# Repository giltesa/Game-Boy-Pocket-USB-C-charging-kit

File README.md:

# Game Boy Pocket USB-C Charging Kit

( This project is a fork from my  )

The **Game Boy Pocket USB-C Charging Kit** is a circuit that allows you to charge a **Nintendo Game Boy Pocket** by **USB-C** and use a **Li-ion** battery instead of AA batteries.

This circuit includes the famous **TP4056** and **DW01A**. The first one is the device in charge of charging the battery, and the second one is protecting the lifetime of the battery of the over-discharge.

This kit includes two boards. If you want to install it easy, it's enough with the main board which doesn't need any cable for working. However, if you want to have the status LEDs in the same place as the original status LED, then you will need to solder the second board and joint both with 3 cables. You can choose the best option for you.

This kit contains 3 boards:

- USB-C board
- Main board
- LEDs board

## Youtube:

Game Boy Pocket USB-C Charging Kit (Installation)

## Would you like it?

https://shop.giltesa.com/product/game-boy-pocket-usb-c-charging-kit/

## More

- [giltesa.com](https://giltesa.com "giltesa.com")
- [twitter.com](https://twitter.com/giltesa "twitter.com")

## License

This project is licensed under a **Creative Commons** license:
**[Attribution-NonCommercial-ShareAlike 4.0 International (CC BY-NC-SA 4.0) ](https://creativecommons.org/licenses/by-nc-sa/4.0/)**

Check the [LICENSE.md](LICENSE.md) for more information.

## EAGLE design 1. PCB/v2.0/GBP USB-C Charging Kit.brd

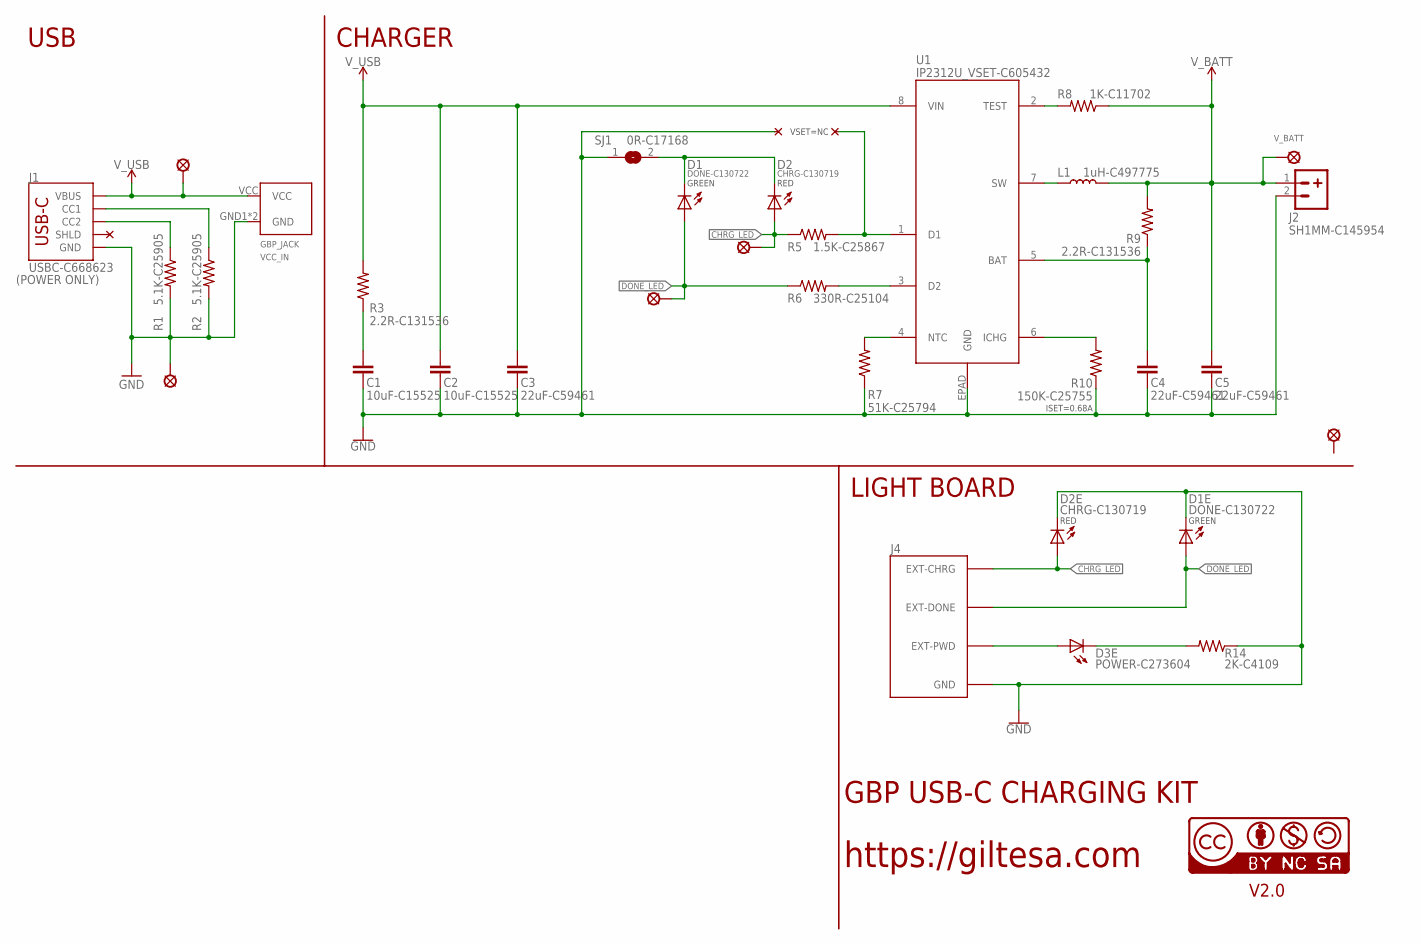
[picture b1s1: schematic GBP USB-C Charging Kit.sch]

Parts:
C1, C2: 10uF-C15525; C0402_S
C3, C4, C5: 22uF-C59461; C0603_S
D1, D1E: DONE-C130722; L0402
D2, D2E: CHRG-C130719; L0402
D3E: POWER-C273604; L0402
GBP_JACK: VCC_IN; GBP_POWER_JACK_DIP
J1: USBC-C668623; USB-C_6P
J2: SH1MM-C145954; JST-2-1MM-SMD_RIGHT
J4: GBP_LED_V2
L1: 1uH-C497775; PSPMAA0402
R1, R2: 5.1K-C25905; R0402
R3, R9: 2.2R-C131536; R0402
R5: 1.5K-C25867; R0402
R6: 330R-C25104; R0402
R7: 51K-C25794; R0402
R8: 1K-C11702; R0402
R10: 150K-C25755; R0402
R14: 2K-C4109; R0402
SJ1: 0R-C17168; JUMPER-SMD_0402
U1: IP2312U_VSET-C605432; IP2312
U$1: V_BATT; PAD_1.25
U$2: SOLDER_PAD-2.0; SOLDER_PAD_2.0
U$12: PAD_2.0
U$17: CC-NC-BCNIX; CC-NC-B_NIX
U$24: CHRG_LED; SOLDER_PAD_1.3
U$25: DONE_LED; SOLDER_PAD_1.3
U$41: PAD_1.25

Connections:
CHRG_LED: D2.A, D2E.A, J4.EXT-CHRG, R5.1, U$24.P$1
DONE_LED: D1.A, D1E.A, J4.EXT-DONE, R6.1, U$25.P$1
GND: C1.1, C2.1, C3.1, C4.1, C5.1, D1E.C, D2E.C, GBP_JACK.GND1 (GND), GBP_JACK.GND2 (GND), J1.A12-GND (GND), J1.B12-GND (GND), J2.2, J4.GND, R1.2, R2.2, R7.1, R10.1, R14.1, SJ1.1, U1.EPAD (GND), U$12.P$1
unnamed: D1.C, D2.C, SJ1.2
unnamed: J1.B5 (CC2), R1.1
unnamed: R8.2, U1.2 (TEST)
unnamed: D3E.A, J4.EXT-PWD, J4.EXT-PWD' (EXT-PWD)
unnamed: D3E.C, R14.2
unnamed: J1.A5 (CC1), R2.1
unnamed: C4.2, R9.1, U1.5 (BAT)
unnamed: C1.2, R3.1
unnamed: R5.2, U1.1 (D1)
unnamed: R7.2, U1.4 (NTC)
unnamed: R10.2, U1.6 (ICHG)
unnamed: R6.2, U1.3 (D2)
unnamed: L1.P$1 (1), U1.7 (SW)
V_BATT: C5.2, J2.1, L1.P$2 (2), R8.1, R9.2, U$1.P$1
V_USB: C2.2, C3.2, GBP_JACK.VCC, J1.A9-VBUS (VBUS), J1.B9-VBUS (VBUS), R3.2, U1.8 (VIN), U$41.P$1

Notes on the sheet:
GBP USB-C CHARGING KIT
https://giltesa.com
V2.0
(POWER ONLY)
USB
CHARGER
LIGHT BOARD
ISET=0.68A
GREEN
RED
VSET=NC

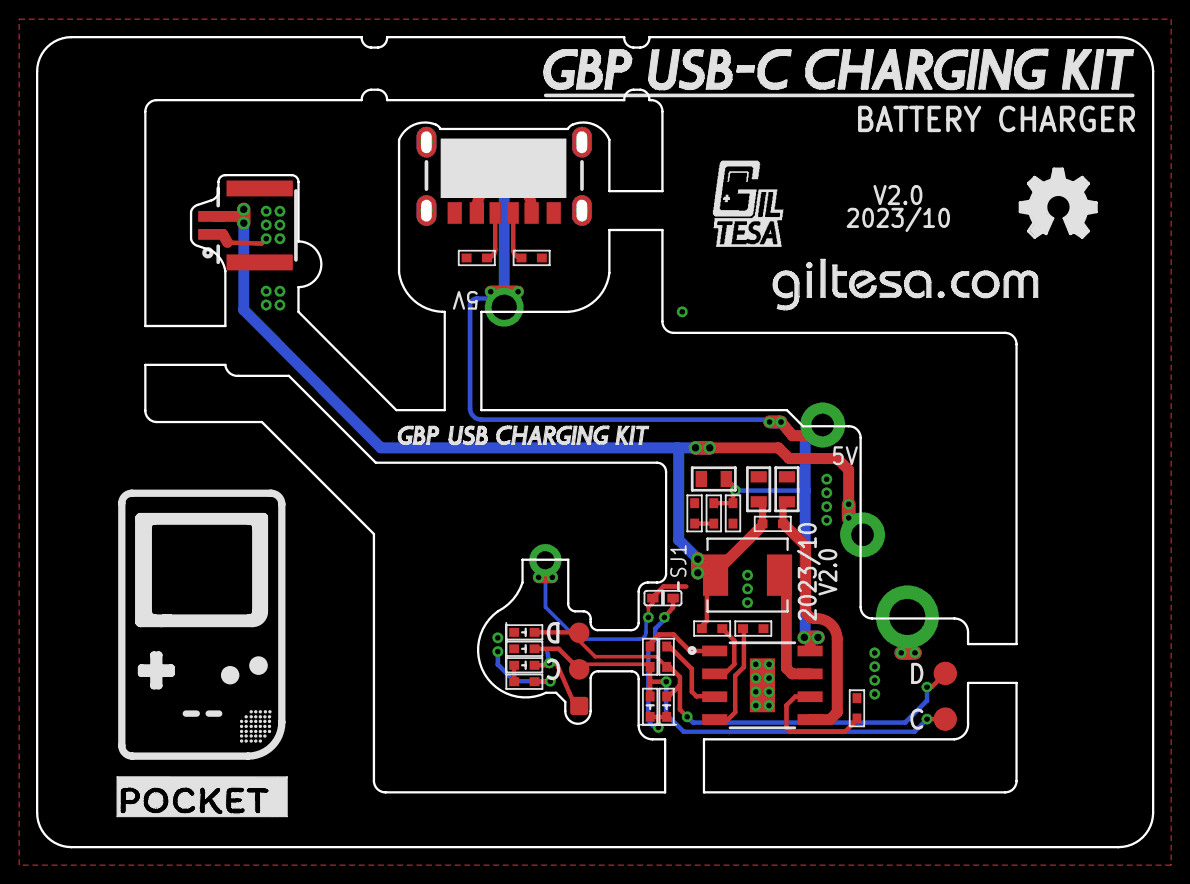
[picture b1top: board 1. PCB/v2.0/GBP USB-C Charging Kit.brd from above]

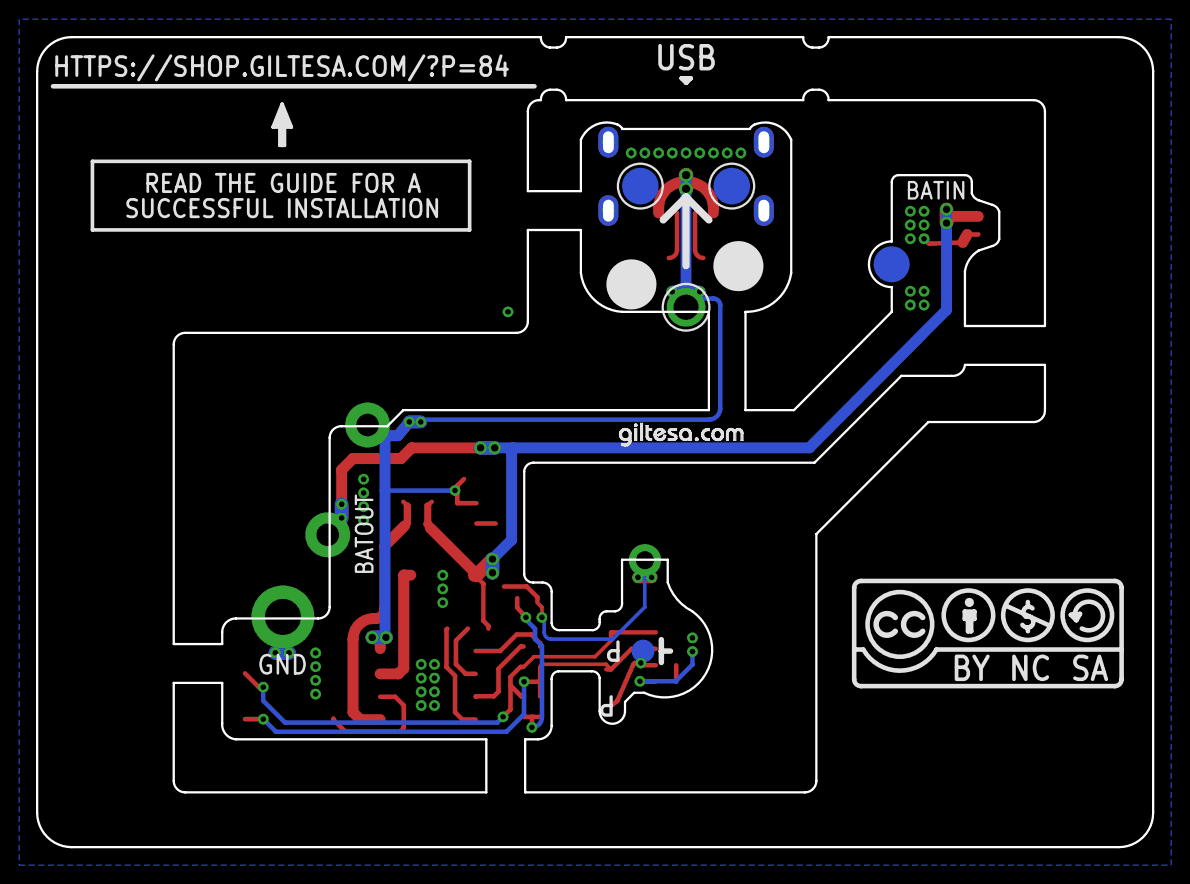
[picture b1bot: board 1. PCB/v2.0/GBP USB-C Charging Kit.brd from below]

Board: 2 copper layers, 62.0 x 45.0 mm, 42 parts (3 on the bottom side), 18 nets.

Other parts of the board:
LOGO1: OSHW_LOGO_FILLX0150-NT; OSHW_FILLX150_NOTEXT
U$3: CC-BY-NC-SA15MM; CC-BY-NC-SA_15MM
U$4: GBP_FRAME
U$7: GBP_FRAME_LOGO
U$10: GILTESA.COM_MASK
U$11: GAME_BOY_POCKET_USB_CHARGING_KIT_NON
U$13: GILTESA_LOGO_MASK_5MM
U$19: GILTESA.COM_MASK_7MM

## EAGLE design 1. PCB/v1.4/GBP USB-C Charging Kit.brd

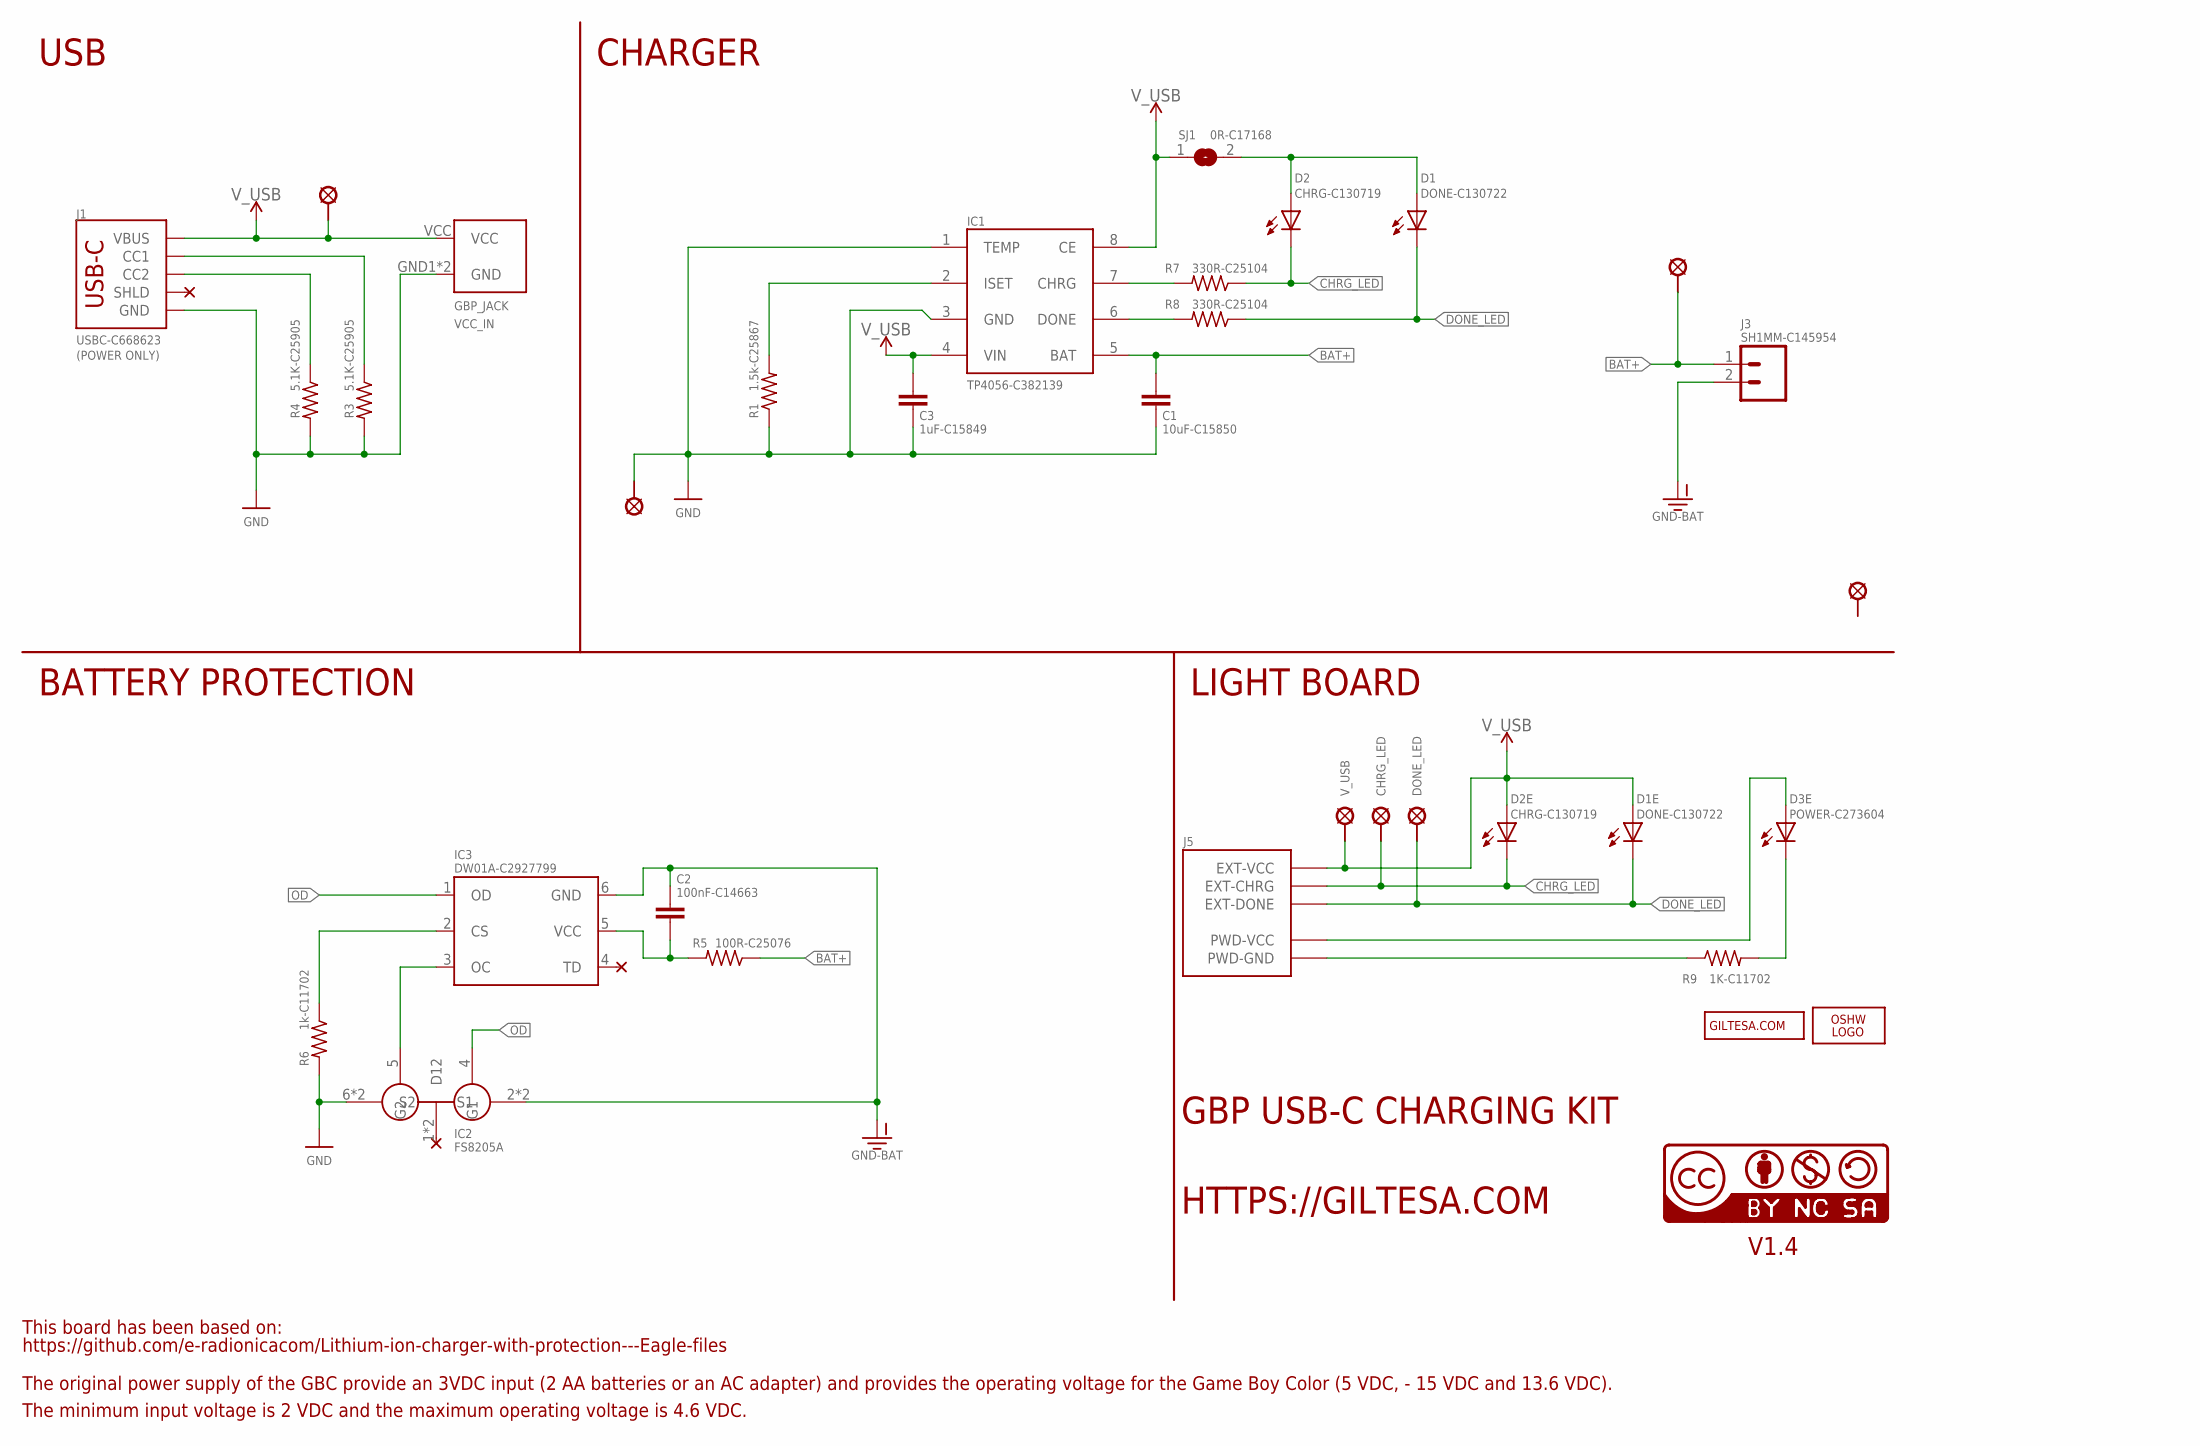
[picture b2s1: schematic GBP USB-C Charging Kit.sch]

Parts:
C1: 10uF-C15850; C0805_S
C2: 100nF-C14663; C0603_S
C3: 1uF-C15849; C0603_S
D1, D1E: DONE-C130722; L0402
D2, D2E: CHRG-C130719; L0402
D3E: POWER-C273604; L0402
GBP_JACK: VCC_IN; GBP_POWER_JACK_DIP
IC1: TP4056-C382139; SOIC-8
IC2: 8205A-C2929075; TSSOP8
IC3: DW01A-C2927799; SOT23-6L
J1: USBC-C668623; USB-C_6P
J3: SH1MM-C145954; JST-2-1MM-SMD_RIGHT
J5: GBP_LED
LOGO2: OSHW_LOGO_FILLX0150-NT; OSHW_FILLX150_NOTEXT
R1: 1.5k-C25867; R0402
R3, R4: 5.1K-C25905; R0402
R5: 100R-C25076; R0402
R6: 1k-C11702; R0402
R7, R8: 330R-C25104; R0402
R9: 1K-C11702; R0402
SJ1: 0R-C17168; JUMPER-SMD_0402
U$2: PAD_2.0
U$3, U$41: PAD_1.25
U$6: CC-BY-NC-SA15MM; CC-BY-NC-SA_15MM
U$12: SOLDER_PAD-2.0; SOLDER_PAD_2.0
U$16: GILTESA.COM_MASK; GILTESA.COM_MASK_15MM
U$24: CHRG_LED; SOLDER_PAD_1.3
U$25: DONE_LED; SOLDER_PAD_1.3
U$26: V_USB; SOLDER_PAD_1.3

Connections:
BAT+: C1.1, IC1.5 (BAT), J3.1, R5.1, U$3.P$1
CHRG: IC1.7 (CHRG), R7.2
CHRG_LED: D2.C, D2E.C, J5.EXT-CHRG, R7.1, U$24.P$1
DONE: IC1.6 (DONE), R8.2
DONE_LED: D1.C, D1E.C, J5.EXT-DONE, R8.1, U$25.P$1
GND: C1.2, C3.2, GBP_JACK.GND1 (GND), GBP_JACK.GND2 (GND), IC1.1 (TEMP), IC1.3 (GND), IC2.6 (S2), IC2.7 (S2), J1.GND1 (GND), J1.GND2 (GND), R1.1, R3.2, R4.2, R6.2, U$2.P$1
GND-BAT: C2.1, IC2.2 (S1), IC2.3 (S1), IC3.6 (GND), J3.2
ISET: IC1.2 (ISET), R1.2
unnamed: IC3.2 (CS), R6.1
unnamed: IC2.5 (G2), IC3.3 (OC)
unnamed: J1.B5 (CC2), R4.1
unnamed: D1.A, D2.A, SJ1.2
unnamed: D3E.C, R9.2
unnamed: J1.A5 (CC1), R3.1
OD: IC2.4 (G1), IC3.1 (OD)
PWD-GND: J5.PWD-GND, J5.PWD-GND' (PWD-GND), R9.1
PWD-VCC: D3E.A, J5.PWD-VCC, J5.PWD-VCC' (PWD-VCC)
VCC-DW: C2.2, IC3.5 (VCC), R5.2
V_USB: C3.1, D1E.A, D2E.A, GBP_JACK.VCC, IC1.4 (VIN), IC1.8 (CE), J1.VBUS1 (VBUS), J1.VBUS2 (VBUS), J5.EXT-VCC, SJ1.1, U$26.P$1, U$41.P$1

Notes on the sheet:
GBP USB-C CHARGING KIT
HTTPS://GILTESA.COM
V1.4
(POWER ONLY)
USB
CHARGER
BATTERY PROTECTION
LIGHT BOARD
IC2
FS8205A
https://github.com/e-radionicacom/Lithium-ion-charger-with-protection---Eagle-files
This board has been based on:
The original power supply of the GBC provide an 3VDC input (2 AA batteries or an AC adapter) and provides the operating voltage for the Game Boy Color (5 VDC, - 15 VDC and 13.6 VDC).
The minimum input voltage is 2 VDC and the maximum operating voltage is 4.6 VDC.

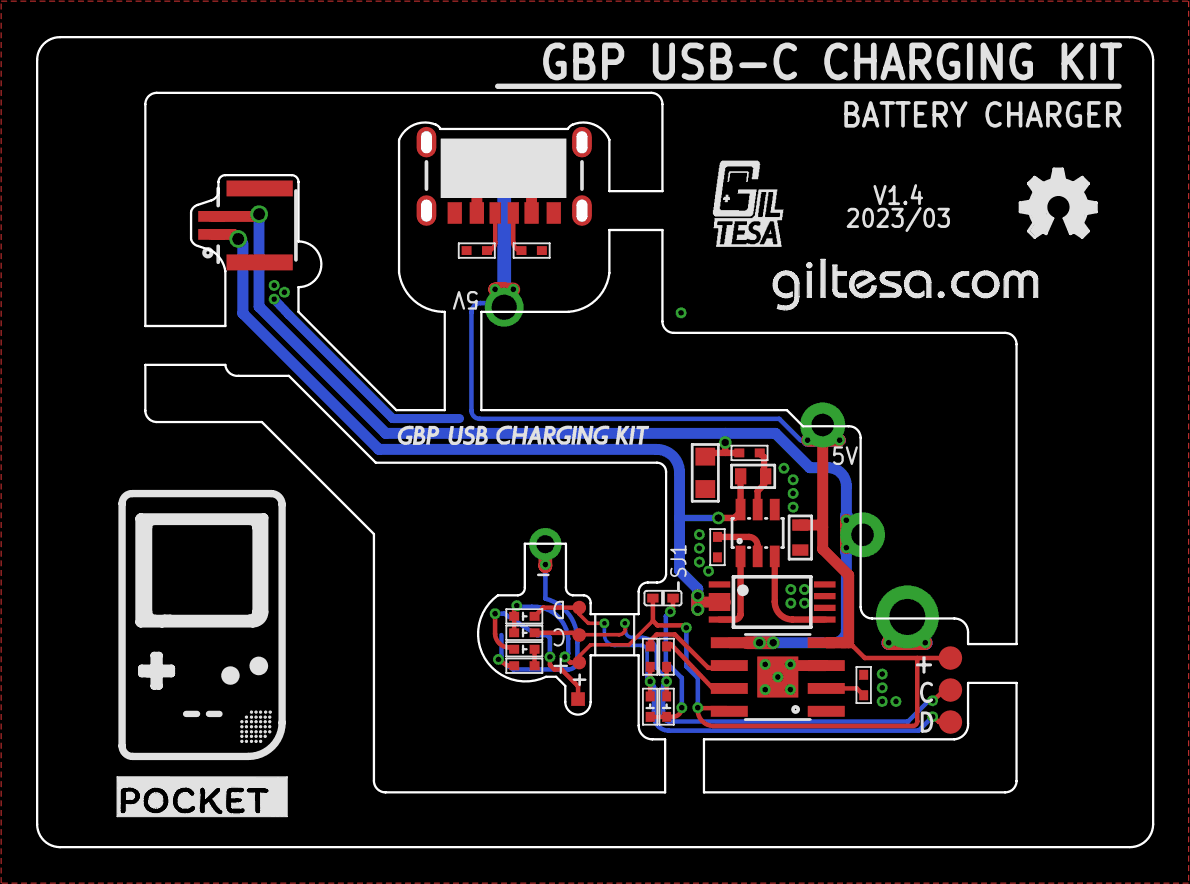
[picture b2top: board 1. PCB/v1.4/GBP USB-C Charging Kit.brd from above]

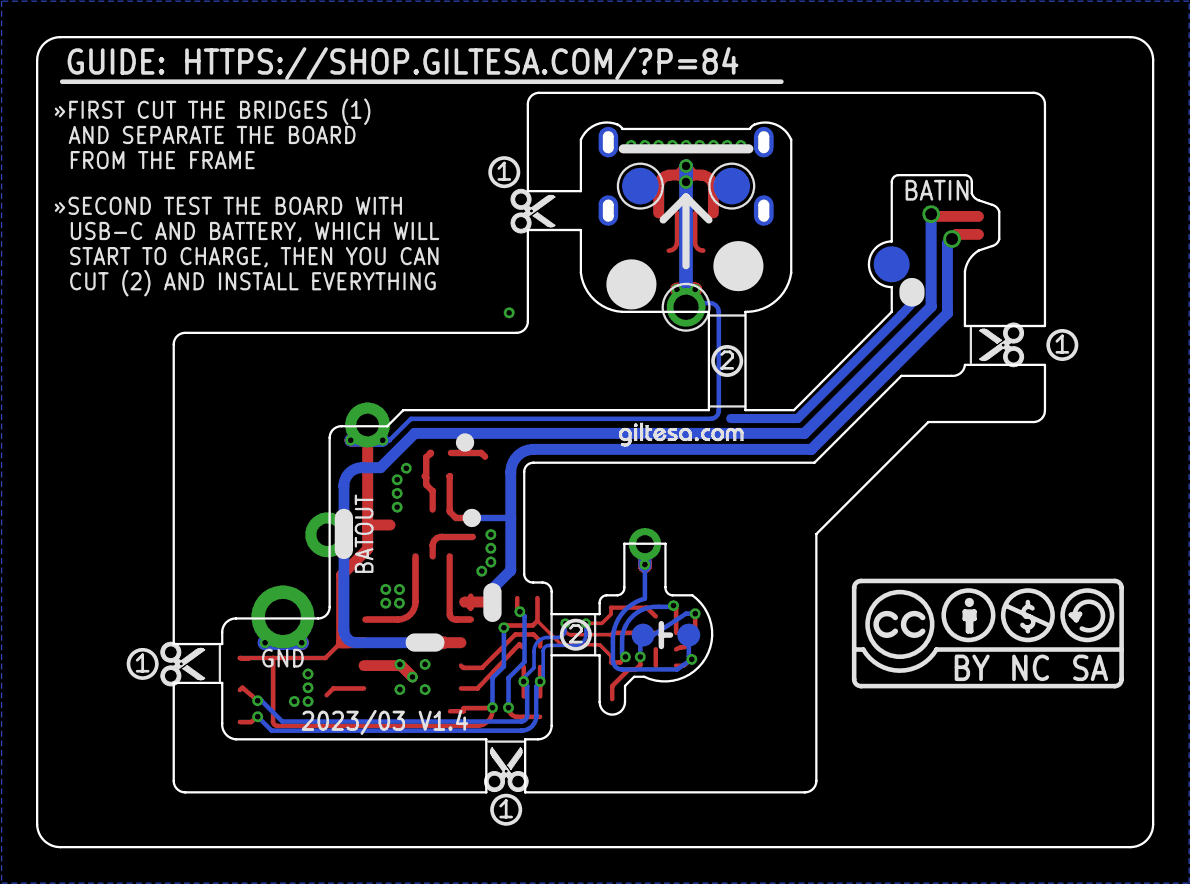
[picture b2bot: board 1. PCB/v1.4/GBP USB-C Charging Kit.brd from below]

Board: 2 copper layers, 62.0 x 45.0 mm, 51 parts (13 on the bottom side), 19 nets.

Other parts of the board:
U$1, U$8, U$9, U$10: SCISSOR_ONE
U$4: GAME_BOY_POCKET_USB_CHARGING_KIT_NON
U$7: GAME_BOY_POCKET
U$13: GILTESA_LOGO_MASK_5MM
U$14, U$18: SCISSOR_TWO
U$17, U$21, U$43, U$44: SCISSOR
U$19: GILTESA.COM_MASK_7MM@1
U$28: GAME_BOY_POCKET_2
U$37, U$38: CC-NC-BCNIX; CC-NC-B_NIX

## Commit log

2021-03-09 no message
2022-08-22 v1.2
2023-03-23 v1.3
2023-08-14 v1.4
2023-10-29 v2.0

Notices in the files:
parts and their libraries:
SparkFun: Licensing: CC v3.0 Share-Alike You are welcome to use this library for commercial purposes.
SparkFun-PowerSymbols: Licensing: Creative Commons ShareAlike 4.0 International - https://creativecommons.org/licenses/by-sa/4.0
cc-by-nc-sa: All hardware is licensed under the Creative Commons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
